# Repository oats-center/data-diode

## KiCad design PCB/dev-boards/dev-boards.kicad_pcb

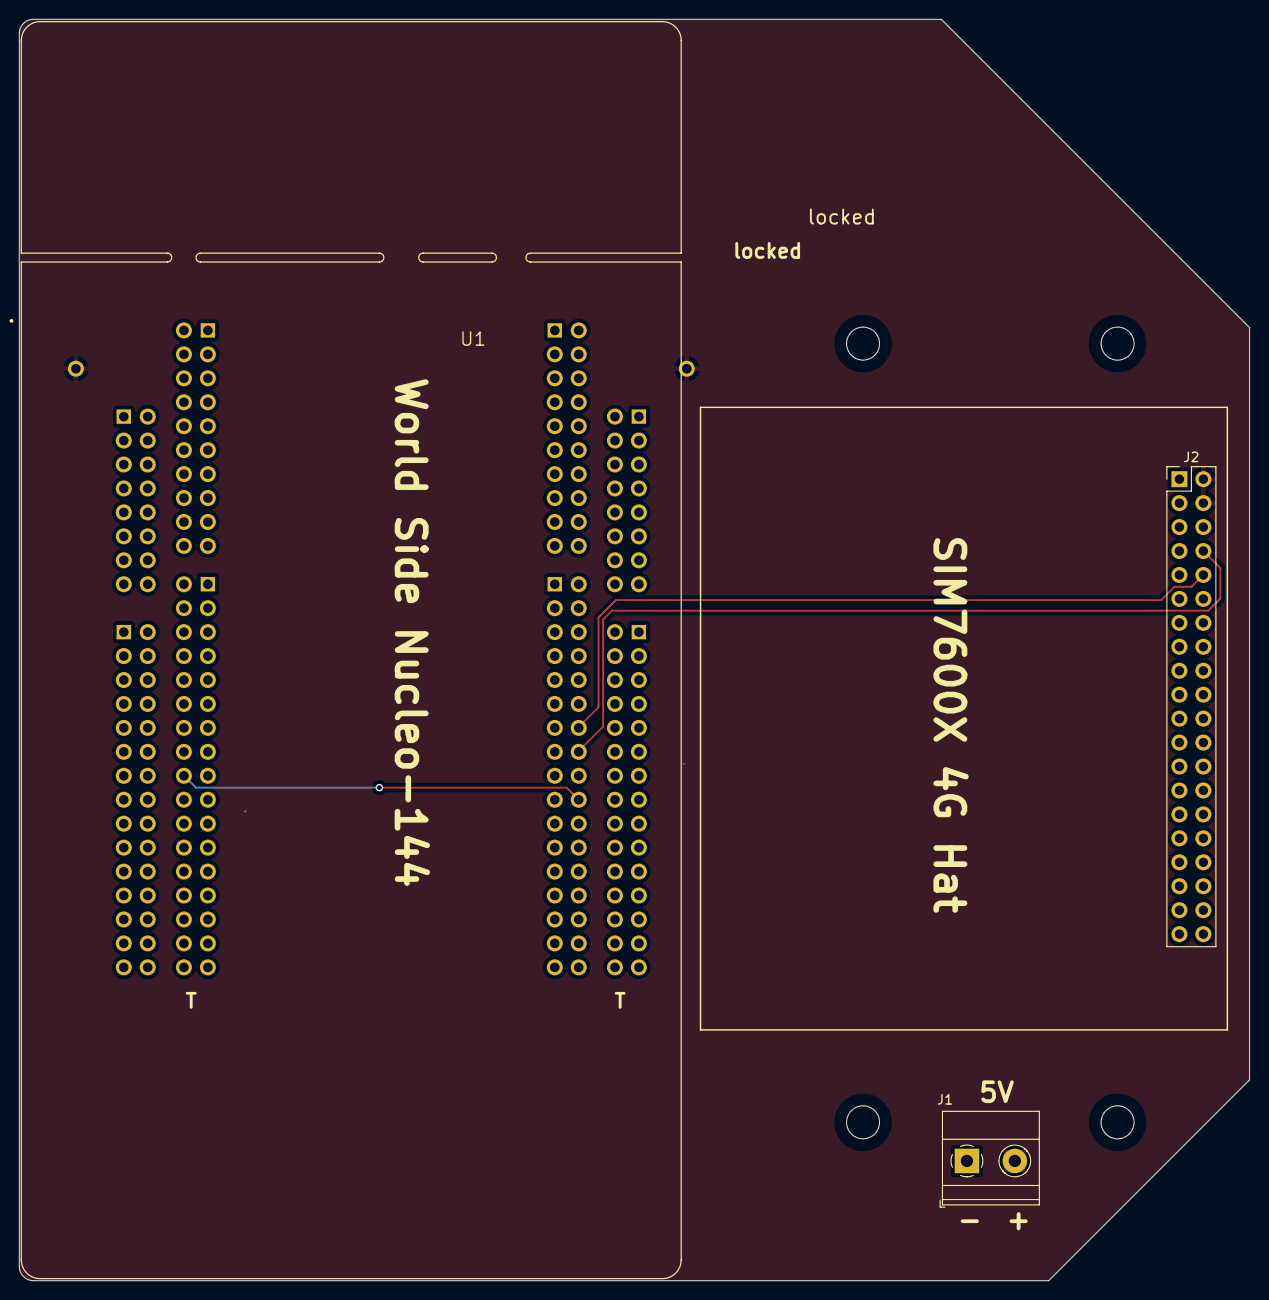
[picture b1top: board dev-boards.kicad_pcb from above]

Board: 2 copper layers, 130.5 x 133.8 mm, 9 parts (1 on the bottom side), 5 nets.

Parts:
H1, H2, H3, H4: MountingHole; MountingHole_3.5mm
J1: 5V Input; TerminalBlock_Phoenix_MKDS-1,5-2-5.08_1x02_P5.08mm_Horizont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
J2: SIM7600 Cell Header; PinHeader_2x20_P2.54mm_Vertical
N1: Housing; oats_logo
U1, U2: NUCLEO-F429ZI; MODULE_NUCLEO-F429ZI

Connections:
+5V: J1.2, J2.2, J2.4, U1.CN11_6 (E5V), U2.CN11_6 (E5V)
/M_RX_TX: J2.10, U1.CN10_14 (D1/USART_A_TX)
/M_TX_RX: J2.8, U1.CN10_16 (D0/USART_A_RX)
/TSC Side Sheet/D_TX: U1.CN10_20 (D41/TIMER_A_ETR), U2.CN10_18 (D42/TIMER_A_PWM1N)
GND: J1.1, J2.6, J2.9, J2.14, J2.20, J2.25, J2.30, J2.34, J2.39, U1.CN7_8 (GND_CN7), U1.CN8_11 (GND_CN8), U1.CN8_13 (GND_CN8), U1.CN9_12 (GND_CN9), U1.CN9_23 (GND_CN9), U1.CN10_3 (AGND_CN10), U1.CN10_5 (GND_CN10), U1.CN10_17 (GND_CN10), U1.CN10_22 (GND_CN10), U1.CN10_27 (GND_CN10), U2.CN7_8 (GND_CN7), U2.CN8_11 (GND_CN8), U2.CN8_13 (GND_CN8), U2.CN9_12 (GND_CN9), U2.CN9_23 (GND_CN9), U2.CN10_3 (AGND_CN10), U2.CN10_5 (GND_CN10), U2.CN10_17 (GND_CN10), U2.CN10_22 (GND_CN10), U2.CN10_27 (GND_CN10)

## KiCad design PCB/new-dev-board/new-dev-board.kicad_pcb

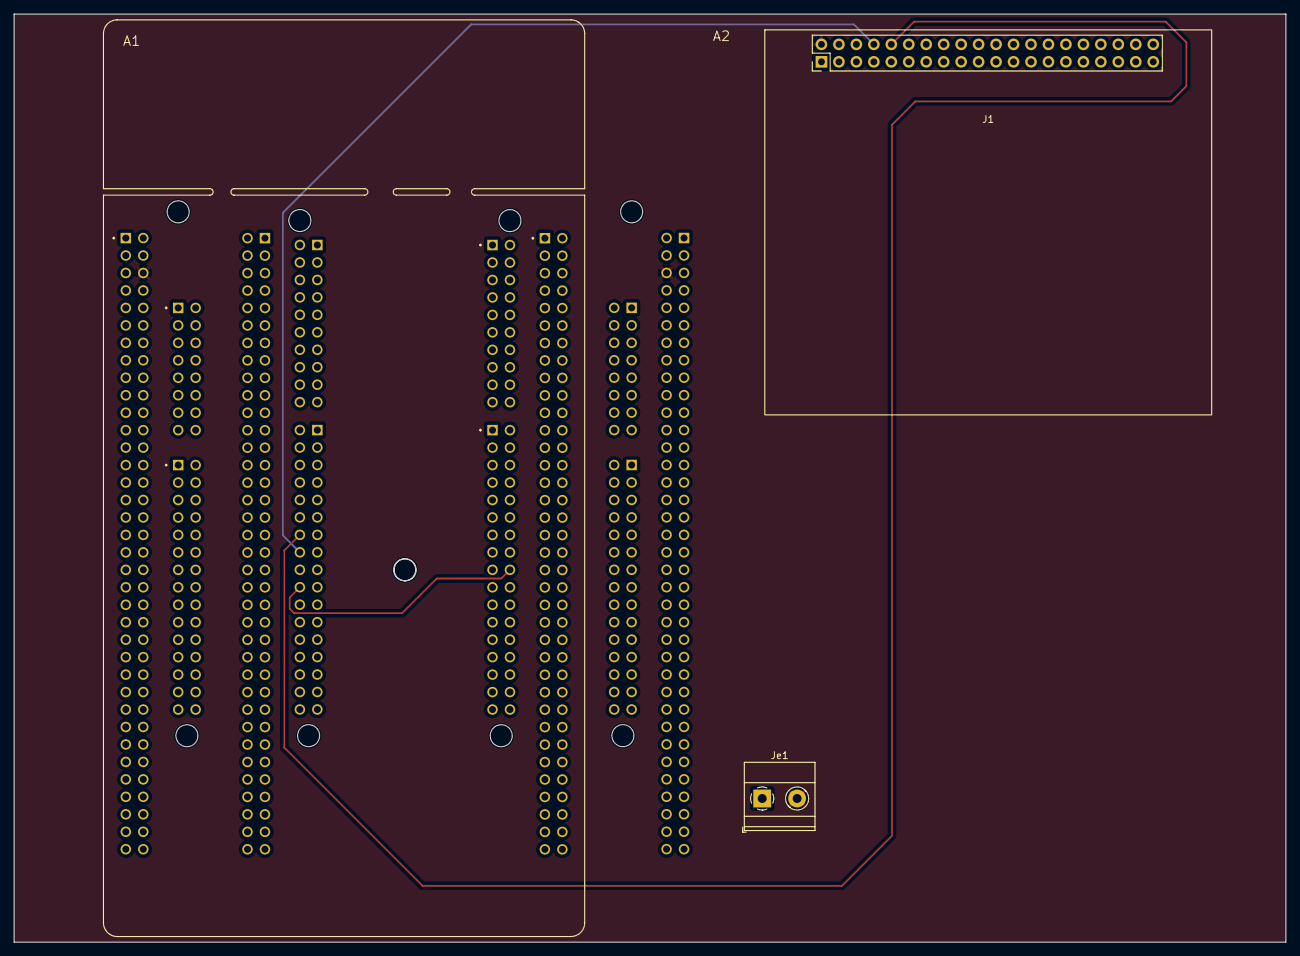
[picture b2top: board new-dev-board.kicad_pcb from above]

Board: 2 copper layers, 185.0 x 135.0 mm, 4 parts (1 on the bottom side), 13 nets.

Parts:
A1, A2: NUCLEO-F767ZI
J1: SIM7600
Je1: Power_Connector; TerminalBlock_Phoenix_MKDS-1,5-2-5.08_1x02_P5.08mm_Horizont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

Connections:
/TSC_STM/E5V: A1.CN11_6 (E5V), A2.CN11_6 (E5V), J1.2, Je1.2
/TSC_STM/GND: A1.CN8_11 (GND_CN8), A1.CN8_13 (GND_CN8), A2.CN8_11 (GND_CN8), A2.CN8_13 (GND_CN8), J1.9, Je1.1
/TSC_STM/UART7_TX: A1.CN10_18 (UART7_TX), A2.CN10_20 (UART7_RX)
/WorldSide/UART6_RX: A2.CN10_16 (D0/USART_A_RX), J1.8
/WorldSide/UART6_TX: A2.CN10_14 (D1/USART_A_TX), J1.10
unnamed: A1.CN11_8 (GND_CN11), A1.CN11_19 (GND_CN11), A1.CN11_20 (GND_CN11), A1.CN11_22 (GND_CN11), A1.CN11_49 (GND_CN11), A1.CN11_60 (GND_CN11), A1.CN11_71 (GND_CN11), A1.CN11_72 (GND_CN11)
unnamed: A1.CN12_9 (GND_CN12), A1.CN12_20 (GND_CN12), A1.CN12_39 (GND_CN12), A1.CN12_54 (GND_CN12), A1.CN12_63 (GND_CN12), A1.CN12_71 (GND_CN12), A1.CN12_72 (GND_CN12)
unnamed: A1.CN9_12 (GND_CN9), A1.CN9_23 (GND_CN9)
unnamed: A1.CN10_5 (GND_CN10), A1.CN10_17 (GND_CN10), A1.CN10_22 (GND_CN10), A1.CN10_27 (GND_CN10)
unnamed: A2.CN11_8 (GND_CN11), A2.CN11_19 (GND_CN11), A2.CN11_20 (GND_CN11), A2.CN11_22 (GND_CN11), A2.CN11_49 (GND_CN11), A2.CN11_60 (GND_CN11), A2.CN11_71 (GND_CN11), A2.CN11_72 (GND_CN11)
unnamed: A2.CN12_9 (GND_CN12), A2.CN12_20 (GND_CN12), A2.CN12_39 (GND_CN12), A2.CN12_54 (GND_CN12), A2.CN12_63 (GND_CN12), A2.CN12_71 (GND_CN12), A2.CN12_72 (GND_CN12)
unnamed: A2.CN9_12 (GND_CN9), A2.CN9_23 (GND_CN9)
unnamed: A2.CN10_5 (GND_CN10), A2.CN10_17 (GND_CN10), A2.CN10_22 (GND_CN10), A2.CN10_27 (GND_CN10)

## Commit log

2023-02-04 mobile: functional base
2023-02-09 Add simple README
2023-02-09 Manish's changes
2023-02-09 Style updates and map
2023-02-09 Update laneManeuvers
2023-02-09 Build static output
2023-02-09 Added NATS directory
2023-02-09 Fix README merge typos
2023-02-09 Fix sizing on mobile
2023-02-09 Make PWA
2023-02-09 Added NATS_modified
2023-02-09 nats_map_spat_parser.py forced to a value
2023-02-13 Re-write framework
2023-02-14 tsc_side_async_programming
2023-02-14 async_changes
2023-02-15 serial_rx
2023-02-15 Base64 based protocol
2023-02-16 cmd file and async tx-rx with base64
2023-02-16 Add MemoryBuffer
2023-02-16 Typo
2023-02-17 vendor CircularBuffer
2023-02-17 membuf changes and compilation fix
2023-02-17 Use cpp and proper cast
2023-02-17 New modem client
2023-02-17 Modem init
2023-02-18 changes upto state 10
2023-02-18 NATS updates
2023-02-19 changes_upto_publish
2023-02-27 Async client updates
2023-02-28 unique_id_bug
2023-02-28 SET_APN_STATE_ADDITION
2023-03-01 if condition bug
2023-03-01 Added start to PCB
2023-03-02 TCP RX bug
2023-03-02 membuf_first(&rx) line removed
2023-03-03 new-dev-board
2023-03-03 removed power traces. added pwr plane
2023-03-03 added 2 mount holes
2023-03-03 PCB board updates
2023-03-05 LED_NETCLOSE_RESET_
2023-03-05 Connect topic change.
2023-03-07 comment_discussions
2023-03-08 Added diode stream script.
2023-03-22 Update PCB for JLCPCB
2023-04-25 PCB: Edits for 3d box
2024-01-05 Data Diode final codebase.
2024-01-05 Added report.
